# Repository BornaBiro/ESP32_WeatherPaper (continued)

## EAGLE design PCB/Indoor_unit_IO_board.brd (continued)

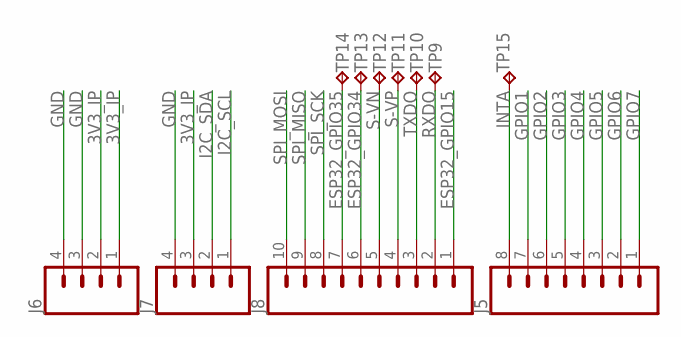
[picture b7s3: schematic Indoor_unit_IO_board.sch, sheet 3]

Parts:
J5: CONN_08"; 1X08
J6, J7: CONN_04; 1X04
J8: CONN_10"; 1X10
TP9, TP10, TP11, TP12, TP13, TP14, TP15: TPTP15R; TP15R

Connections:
3V3_IP: J6.1, J6.2, J7.3; also elsewhere on the board
ESP32_GPIO15: J8.1; also elsewhere on the board
ESP32_GPIO34: J8.6, TP13.TP
ESP32_GPIO35: J8.7, TP14.TP
GND: J6.3, J6.4, J7.4; also elsewhere on the board
GPIO1: J5.7; also elsewhere on the board
GPIO2: J5.6; also elsewhere on the board
GPIO3: J5.5; also elsewhere on the board
GPIO4: J5.4; also elsewhere on the board
GPIO5: J5.3; also elsewhere on the board
GPIO6: J5.2; also elsewhere on the board
GPIO7: J5.1; also elsewhere on the board
I2C_SCL: J7.1; also elsewhere on the board
I2C_SDA: J7.2; also elsewhere on the board
INTA: J5.8, TP15.TP
RXDO: J8.2, TP9.TP
S-VN: J8.5, TP12.TP
S-VP: J8.4, TP11.TP
SPI_MISO: J8.9; also elsewhere on the board
SPI_MOSI: J8.10; also elsewhere on the board
SPI_SCK: J8.8; also elsewhere on the board
TXDO: J8.3, TP10.TP

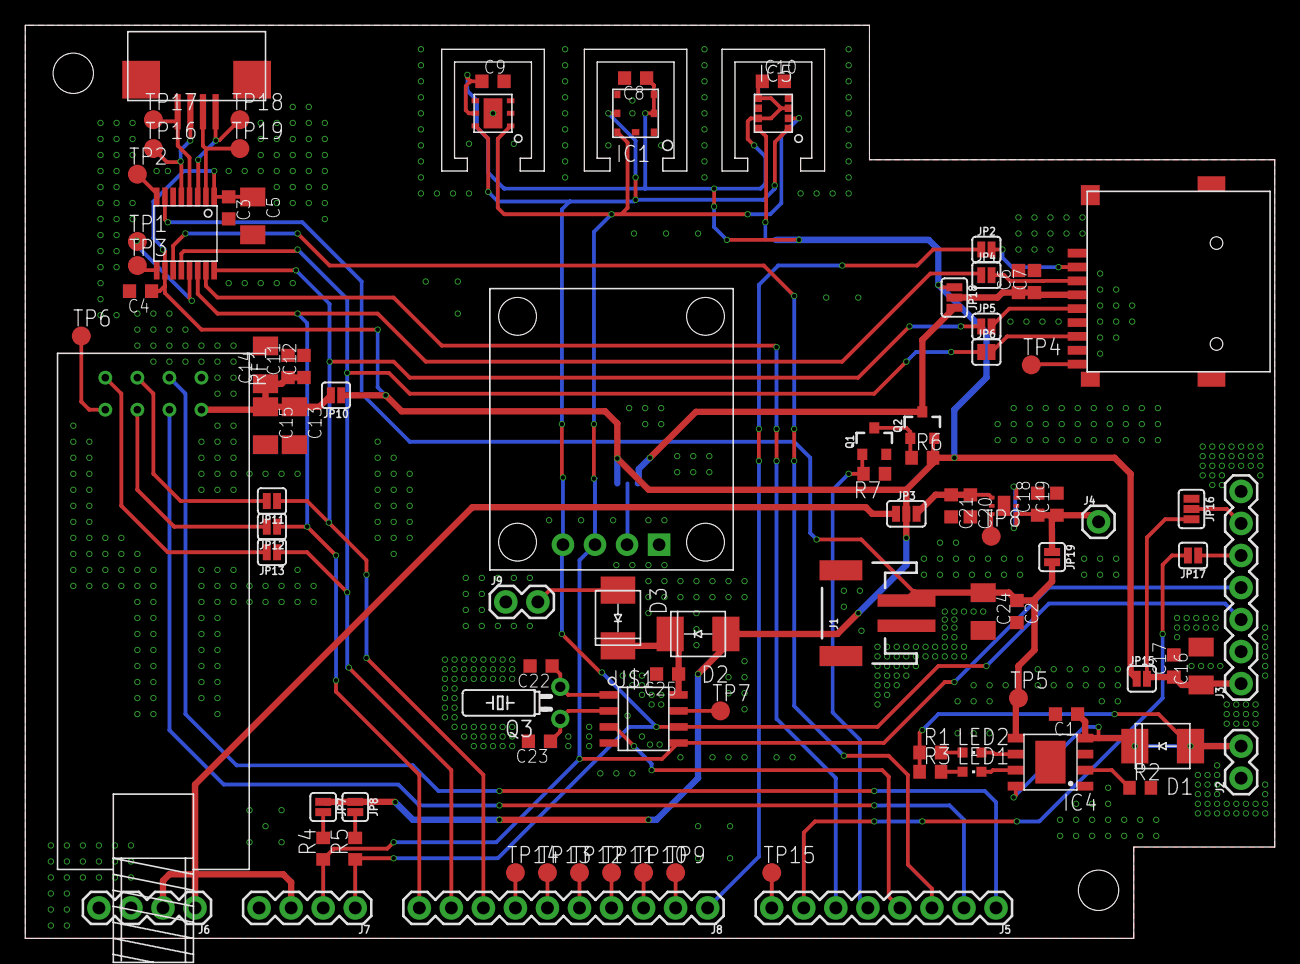
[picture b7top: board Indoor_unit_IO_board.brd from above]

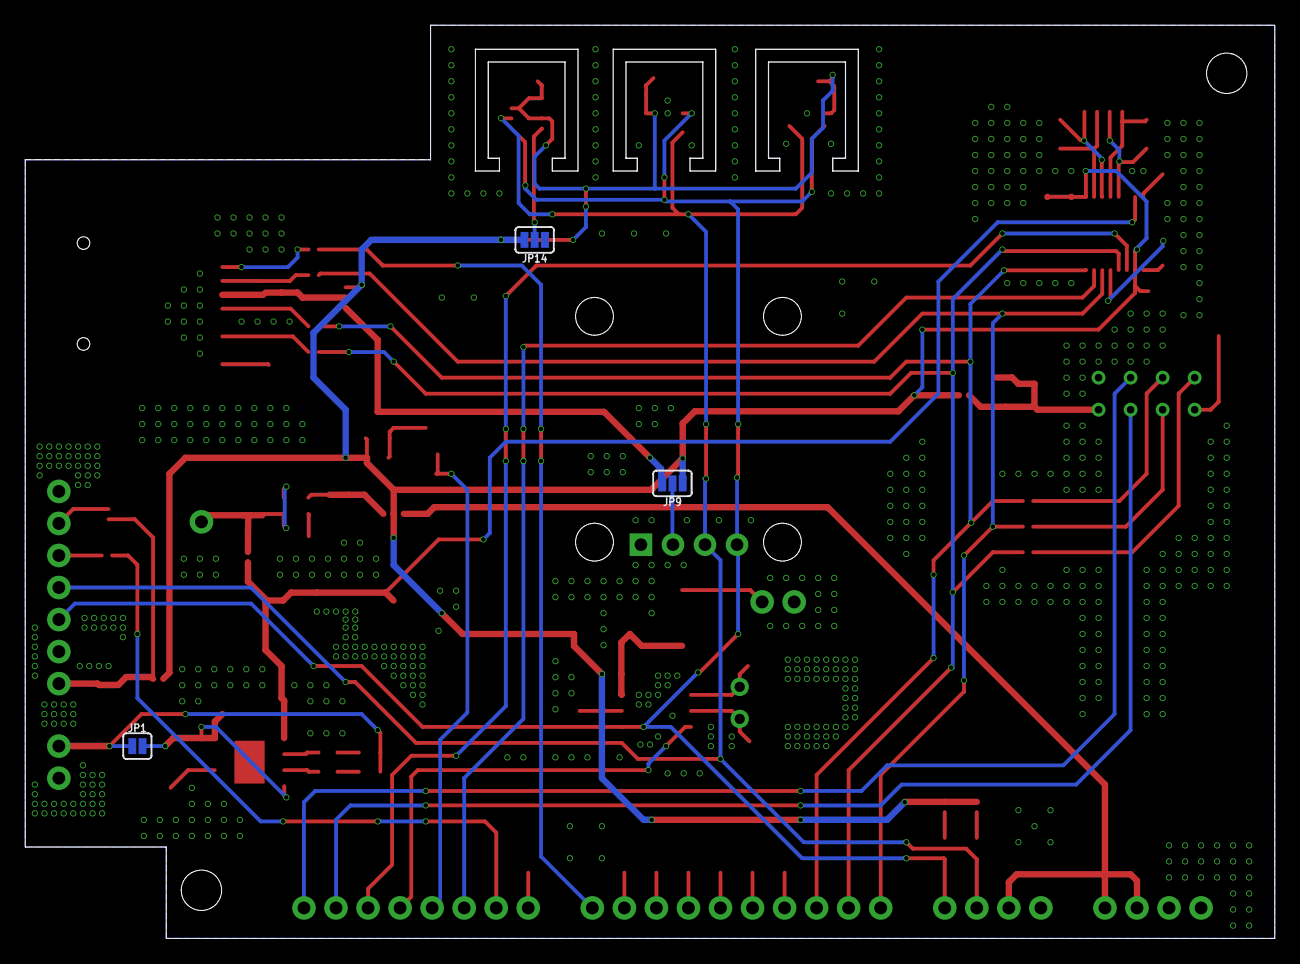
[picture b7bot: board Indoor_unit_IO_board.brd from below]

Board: 2 copper layers, 99.1 x 72.4 mm, 98 parts (3 on the bottom side), 66 nets.

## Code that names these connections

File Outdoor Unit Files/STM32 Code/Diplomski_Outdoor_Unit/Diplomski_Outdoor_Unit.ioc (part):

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Mcu.Name=STM32L073C(B-Z)Tx
Mcu.Package=LQFP48
Mcu.UserName=STM32L073CZTx
PA0.Mode=IN0
PA0.Signal=ADC_IN0
PA1.Mode=IN1
PA1.Signal=ADC_IN1
PA10.GPIOParameters=GPIO_PuPd,GPIO_Label
PA10.GPIO_Label=WS_DIN
PA10.GPIO_PuPd=GPIO_NOPULL
PA10.Signal=GPIO_Input
PA13.Mode=Serial_Wire
PA13.Signal=SYS_SWDIO
PA14.Mode=Serial_Wire
PA14.Signal=SYS_SWCLK
PA2.Mode=Asynchronous
PA2.Signal=USART2_TX
PA3.Mode=Asynchronous
PA3.Signal=USART2_RX
PA4.Mode=IN4
PA4.Signal=ADC_IN4
PA5.Mode=Full_Duplex_Master
PA5.Signal=SPI1_SCK
PA6.Mode=Full_Duplex_Master
PA6.Signal=SPI1_MISO
PA7.Mode=Full_Duplex_Master
PA7.Signal=SPI1_MOSI
PA8.GPIOParameters=GPIO_PuPd
PA8.GPIO_PuPd=GPIO_PULLUP
PA8.Signal=GPXTI8
PA9.GPIOParameters=GPIO_Label
PA9.GPIO_Label=BAT_M_EN
PA9.Signal=GPIO_Output
PB1.GPIOParameters=GPIO_PuPd
PB1.GPIO_PuPd=GPIO_PULLUP
PB1.Signal=GPXTI1
PB11.GPIOParameters=GPIO_Label
PB11.GPIO_Label=EN_3V3SW
PB11.Signal=GPIO_Output
PB4.GPIOParameters=GPIO_Speed,GPIO_Label
PB4.GPIO_Label=NRF24_CE
PB4.GPIO_Speed=GPIO_SPEED_FREQ_HIGH
PB4.Signal=GPIO_Output
PB5.GPIOParameters=GPIO_PuPd,GPIO_Label
PB5.GPIO_Label=SI1147_INT
PB5.GPIO_PuPd=GPIO_PULLUP
PB5.Signal=GPIO_Input
PB6.GPIOParameters=GPIO_Speed,GPIO_Label
PB6.GPIO_Label=NRF24_CSN
PB6.GPIO_Speed=GPIO_SPEED_FREQ_HIGH
PB6.Signal=GPIO_Output
PB8.Mode=I2C
PB8.Signal=I2C1_SCL
PB9.Mode=I2C
PB9.Signal=I2C1_SDA
PC14-OSC32_IN.Mode=LSE-External-Oscillator
PC14-OSC32_IN.Signal=RCC_OSC32_IN
PC15-OSC32_OUT.Mode=LSE-External-Oscillator
PC15-OSC32_OUT.Signal=RCC_OSC32_OUT
PH0-OSC_IN.Mode=HSE-External-Oscillator
PH0-OSC_IN.Signal=RCC_OSC_IN
PH1-OSC_OUT.Mode=HSE-External-Oscillator
PH1-OSC_OUT.Signal=RCC_OSC_OUT
RCC.HSE_VALUE=4000000
RCC.SYSCLKFreq_VALUE=4000000
RCC.SYSCLKSource=RCC_SYSCLKSOURCE_HSE
board=custom

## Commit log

2019-08-15 Dynamic size Json to static
2019-09-30 New Font, touchscreen functions, added wind dir
    Added new font into Sketch, add low power capability, refresh on demand, new function for epoch to time conversion, new touch functions (for 10 inch resistive touch), wind direction indicator and bug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
2021-03-19 Added folder for test codes
    Added test code for touch keyboard input and text box
2021-03-19 Test codes: Keyboard & textbox - Added string size parameter in struct
    Added string size parameter in struct and modified data types in struct
2021-03-19 Test codes: Keyboard & textbox - Almost full functionality of textbox
    Textbox is now working. Still there is still some issues on selecting end of string with touch. And there should be added arrows for navigation though textbox/string.
2021-09-25 Added new fonts, added crowdfunding, added new data in json, added Inkplate library
2021-09-26 Added Touchscreen Controller, code clean up, visual improvements, added rain
2021-09-27 New refresh time, added feedback when data is being refreshed,
2021-09-27 RTC used for clock instead or NTP every time it refreshes, added file for all structs, added code for converting epoch to human T&D, minor code cleanup, sensor struct, better NTP
2021-09-27 Removed old files (touch.h, E_INK.h, .ino file)
2021-09-29 More code cleanup, better parsing current weather data, new structs for current weather and forecast
2021-09-29 New code for parsing and storing 5 days / 3h forecast, more code cleanup and edit
2021-09-30 Transferred openWeatherMaps API functions into library, added function for touch detection in some area, added rounding for temperature, replaced back button position for selected day, structs moved 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
2021-10-01 Added separate files for GUI elements (drawing elements on screen) and for time and date, fixed multiple definitions for icons and fonts, added calculations for avg. wind speed and dir., different BM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
2021-10-01 Fixed bug in avg. wind dir., global Inkplate object in GUI library (also added GUI::init() function), added new icons for buttons (UV, light and solar irradiated power are missing), fixed forecast (n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
2021-10-26 New graphs, new and improved GUI, added external RTC, modified code for new board and board addon (with sensors, TS controller and RTC)
2021-10-26 Added RF communication (just sync for now), fixed graphs (added manual scaling)
2021-10-26 Added function for getting data from RF, fixed bug with RF and touch collision (PB7 on MCP was set to HIGH in loop)
2021-10-27 Added saving data to SD (from indoor and outdoor), reading data from SD and seperate them into variables (only for outdoor)
2021-10-27 Fixed bug with getting data from SD card, added displaying outdoor data on graph.
2021-10-27 Fix on init of TSC2046 driver
2021-10-27 Added graphs for outdoor and indoor data
2021-10-28 Bug fixes includes that includes UV bug, indoor graph bug, clock bug. Added CO2 readings, added battery measurement, added icons on graphs, added selectable graphs
2021-10-28 Added button for sync and for NTP Clock Sync
2021-10-29 Added comments, added graph rewind / forward, added showing all measured data on main screen, added WiFi connection timeout, fixed eeprom wakeup (pointers)
2021-10-29 Changed string while sync, added day FW / RW in graphs, added display to show last outdoor data T&D
2021-11-29 First final version, added .gitignore, added partial updates, fixed bug in forced NTP clock sync, added debug messages
2021-11-29 Split files into folders, added FreeCAD models, added STL files, added PCB files
2022-06-14 Folder structure changed again, added libraires
2022-06-14 RTC and time fix, new wake up time,
    Wake up every 5 minutes.
2022-06-14 CO2 sensor is read every 30 minutes (like weather from Internet)
2022-06-14 Better low power mode I guess?
2022-08-17 Fixed semi-random crashes while fetching and parsing weather data.
    Usually ESP32 crashes every day between 22:00h and 23:00. There was a issue on divide by zero in Weather.cpp, line "_d[i].avgPressure /= nElements".
2022-09-30 Fixed not waking up at the start of the month.
2022-11-02 Embarrassing mistake while reading and setting RTC month.
2023-01-04 Files moved
2023-01-04 Added outdoor unit files, added images.
2023-01-04 Create licence
2023-07-17 Changed solar cell short circuit current to 45mA.
    Old solar cell for measuring solar irradiance was broken due heavy storm, so it needed to be changed, as well as SC current.
2023-07-17 Fine-tuned solar cell SC current.
    Due big variations in Chinese solar cells (especially small ones, like this 40/45mA one), SC current needs to be calibrated. I used www.meteo.hr solar data to calibrate it.
2023-07-20 Added new test code for new graph design.
2025-08-11 Updated to static IP due ISP tech genius.
2025-08-11 Added thingSpeak.
